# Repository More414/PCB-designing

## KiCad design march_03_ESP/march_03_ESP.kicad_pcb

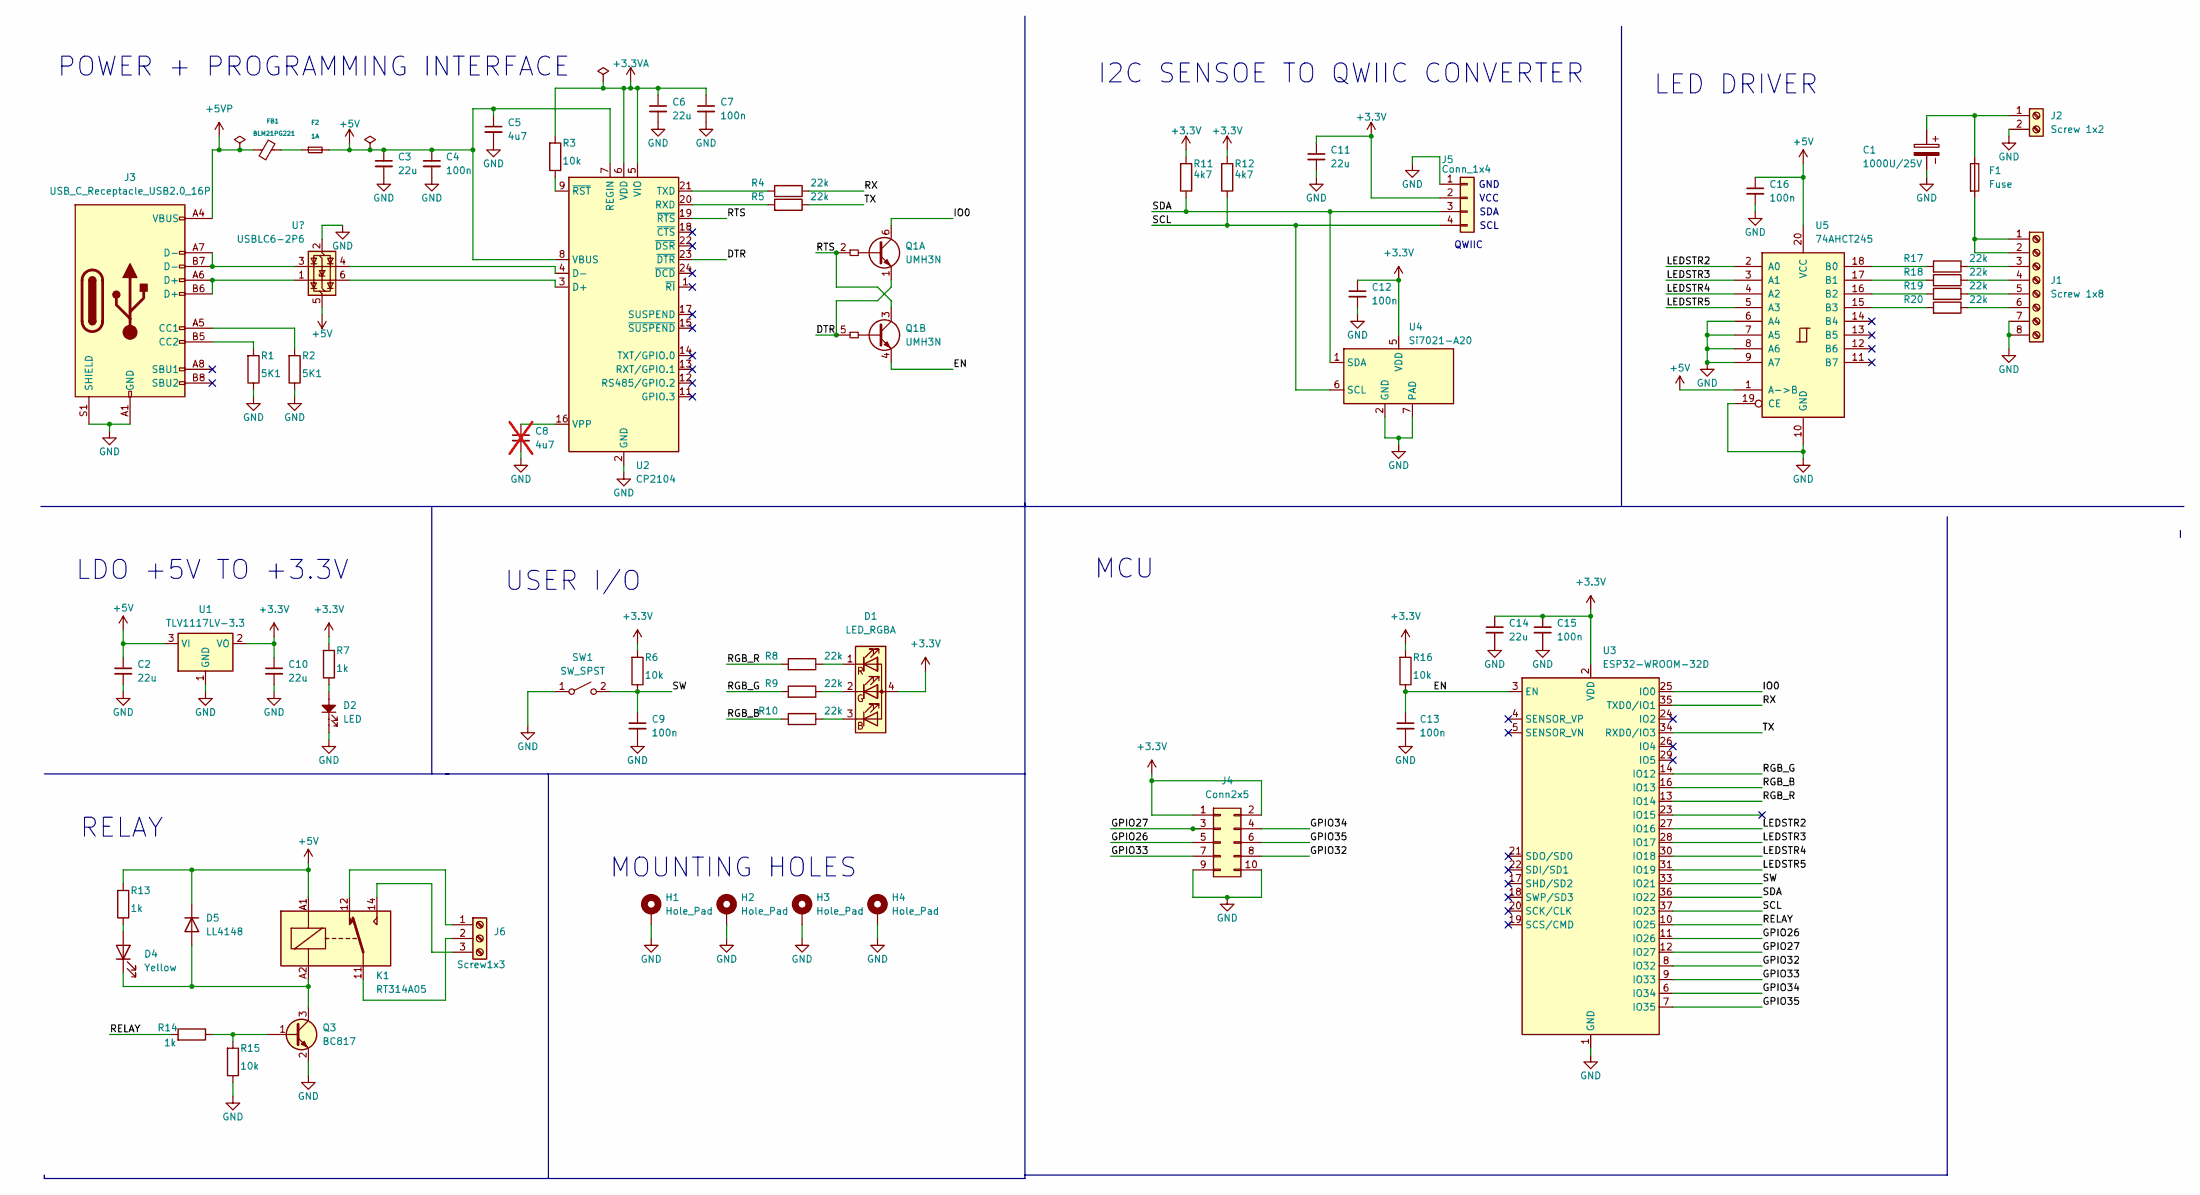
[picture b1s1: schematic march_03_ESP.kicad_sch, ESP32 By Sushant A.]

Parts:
C1: 1000U/25V; CP_Radial_D5.0mm_P2.50mm
C2, C3, C6, C10, C11, C14: 22u; C_0805_2012Metric_Pad1.18x1.45mm_HandSolder
C4, C7, C9, C12, C13, C15, C16: 100n; C_0402_1005Metric_Pad0.74x0.62mm_HandSolder
C5: 4u7; C_0805_2012Metric_Pad1.18x1.45mm_HandSolder
C8: 4u7; C_0805_2012Metric_Pad1.18x1.45mm_HandSolder; not fitted
D1: LED_RGBA; LED_RGB_Wuerth-PLCC4_3.2x2.8mm_150141M173100
D2: LED; LED_0805_2012Metric
D4: Yellow; LED_0603_1608Metric_Pad1.05x0.95mm_HandSolder
D5: LL4148; D_MiniMELF
F1: Fuse; Fuse_0805_2012Metric
F2: 1A; fuse_imp
FB1: BLM21PG221; L_0603_1608Metric_Pad1.05x0.95mm_HandSolder
H1, H2, H3, H4: Hole_Pad; MountingHole_3.2mm_M3_Pad_Via
J1: Screw 1x8; TerminalBlock_Phoenix_MKDS-1,5-8_1x08_P5.00mm_Horizontal
J2: Screw 1x2; TerminalBlock_Phoenix_MKDS-1,5-2-5.08_1x02_P5.08mm_Horizont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
J3: USB_C_Receptacle_USB2.0_16P; USB_C_Receptacle_GCT_USB4105-xx-A_16P_TopMnt_Horizontal
J4: Conn2x5; PinHeader_2x05_P2.54mm_Vertical
J5: Conn_1x4; JST_SH_SM04B-SRSS-TB_1x04-1MP_P1.00mm_Horizontal
J6: Screw1x3; TerminalBlock_Phoenix_MKDS-3-3-5.08_1x03_P5.08mm_Horizontal
K1: RT314A05; Relay_SPDT_Schrack-RT1-16A-FormC_RM5mm
Q1: UMH3N; SOT-363_SC-70-6
Q3: BC817; SOT-23
R1, R2: 5K1; R_0805_2012Metric
R3, R6, R15, R16: 10k; R_0805_2012Metric
R4, R5, R8, R9, R10, R17, R18, R19, R20: 22k; R_0805_2012Metric
R7, R13, R14: 1k; R_0805_2012Metric
R11, R12: 4k7; R_0805_2012Metric
SW1: SW_SPST; SW_Push_1P1T_NO_E-Switch_TL3301NxxxxxG
U1: TLV1117LV-3.3; SOT-223-3_TabPin2
U2: CP2104; QFN-24-1EP_4x4mm_P0.5mm_EP2.6x2.6mm
U3: ESP32-WROOM-32D
U4: Si7021-A20; DFN-6-1EP_3x3mm_P1mm_EP1.5x2.4mm
U5: 74AHCT245; DIP-20_W7.62mm

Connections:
+3.3V: C10.1, C11.1, C12.1, C14.1, C15.1, D1.4 (A), J4.1, J4.2, J5.2, R6.1, R7.1, R11.1, R12.1, R16.1, U1.2 (VO), U3.2 (VDD), U4.5 (VDD)
+3.3VA: C6.1, C7.1, R3.1, U2.5 (VIO), U2.6 (VDD)
+5V: C2.1, C3.1, C4.1, C5.1, C16.1, D5.1 (K), F2.2, K1.A1, R13.1, U1.3 (VI), U2.7 (REGIN), U2.8 (VBUS), U5.1 (A->B), U5.20 (VCC); also elsewhere on the board
+5VP: FB1.1, J3.A4 (VBUS), J3.A9 (VBUS), J3.B4 (VBUS), J3.B9 (VBUS)
/DTR: Q1.1 (E1), Q1.5 (B2), U2.23 (~DTR)
/EN: C13.1, Q1.4 (E2), R16.2, U3.3 (EN)
/GPIO26: J4.5, U3.11 (IO26)
/GPIO27: J4.3, U3.12 (IO27)
/GPIO32: J4.8, U3.8 (IO32)
/GPIO33: J4.7, U3.9 (IO33)
/GPIO34: J4.4, U3.6 (IO34)
/GPIO35: J4.6, U3.7 (IO35)
/IO0: Q1.6 (C1), U3.25 (IO0)
/LEDSTR2: U3.27 (IO16), U5.2 (A0)
/LEDSTR3: U3.28 (IO17), U5.3 (A1)
/LEDSTR4: U3.30 (IO18), U5.4 (A2)
/LEDSTR5: U3.31 (IO19), U5.5 (A3)
/RELAY: R14.1, U3.10 (IO25)
/RGB_B: R10.1, U3.16 (IO13)
/RGB_G: R9.1, U3.14 (IO12)
/RGB_R: R8.1, U3.13 (IO14)
/RTS: Q1.2 (B1), Q1.3 (C2), U2.19 (~RTS)
/RX: R4.2, U3.35 (TXD0/IO1)
/SCL: J5.4, R12.2, U3.37 (IO23), U4.6 (SCL)
/SDA: J5.3, R11.2, U3.36 (IO22), U4.1 (SDA)
/SW: C9.1, R6.2, SW1.2 (B), U3.33 (IO21)
/TX: R5.2, U3.34 (RXD0/IO3)
GND: C1.2, C2.2, C3.2, C4.2, C5.2, C6.2, C7.2, C8.2, C9.2, C10.2, C11.2, C12.2, C13.2, C14.2, C15.2, C16.2, D2.1, H1.1, H2.1, H3.1, H4.1, J1.7, J1.8, J2.2, J3.A1 (GND), J3.A12 (GND), J3.B1 (GND), J3.B12 (GND), J3.S1 (SHIELD), J4.9, J4.10, J5.1, Q3.2 (E), R1.2, R2.2, R15.2, SW1.1 (A), U1.1 (GND), U2.2 (GND), U2.25 (GND), U3.1 (GND), U3.15 (GND), U3.38 (GND), U3.39 (GND), U4.2 (GND), U4.7 (PAD), U5.6 (A4), U5.7 (A5), U5.8 (A6), U5.9 (A7), U5.10 (GND), U5.19 (CE); also elsewhere on the board
unnamed: D1.3 (BK), R10.2
unnamed: D1.2 (GK), R9.2
unnamed: D1.1 (RK), R8.2
unnamed: D2.2, R7.2
unnamed: D4.2 (A), R13.2
unnamed: D4.1 (K), D5.2 (A), K1.A2, Q3.3 (C)
unnamed: F2.1, FB1.2
unnamed: F1.2, J1.1, J1.2
unnamed: J1.3, R17.2
unnamed: J1.4, R18.2
unnamed: J1.5, R19.2
unnamed: J1.6, R20.2
unnamed: C1.1, F1.1, J2.1
unnamed: J3.A5 (CC1), R2.1
unnamed: J3.B5 (CC2), R1.1
unnamed 43: J3.A6 (D+), J3.B6 (D+); also elsewhere on the board
unnamed 44: J3.A7 (D-), J3.B7 (D-); also elsewhere on the board
unnamed: J6.1, K1.12
unnamed: J6.2, K1.11
unnamed: J6.3, K1.14
unnamed: Q3.1 (B), R14.2, R15.1
unnamed 49: U2.3 (D+); also elsewhere on the board
unnamed 50: U2.4 (D-); also elsewhere on the board
unnamed: R5.1, U2.20 (RXD)
unnamed: R4.1, U2.21 (TXD)
unnamed: C8.1, U2.16 (VPP)
unnamed: R3.2, U2.9 (~RST)
unnamed: R17.1, U5.18 (B0)
unnamed: R18.1, U5.17 (B1)
unnamed: R19.1, U5.16 (B2)
unnamed: R20.1, U5.15 (B3)

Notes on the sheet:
LED DRIVER
I2C SENSOE TO QWIIC CONVERTER
VCC
MOUNTING HOLES
SDA
LDO +5V TO +3.3V
POWER + PROGRAMMING INTERFACE
MCU
USER I/O
GND
RELAY
SCL
QWIIC

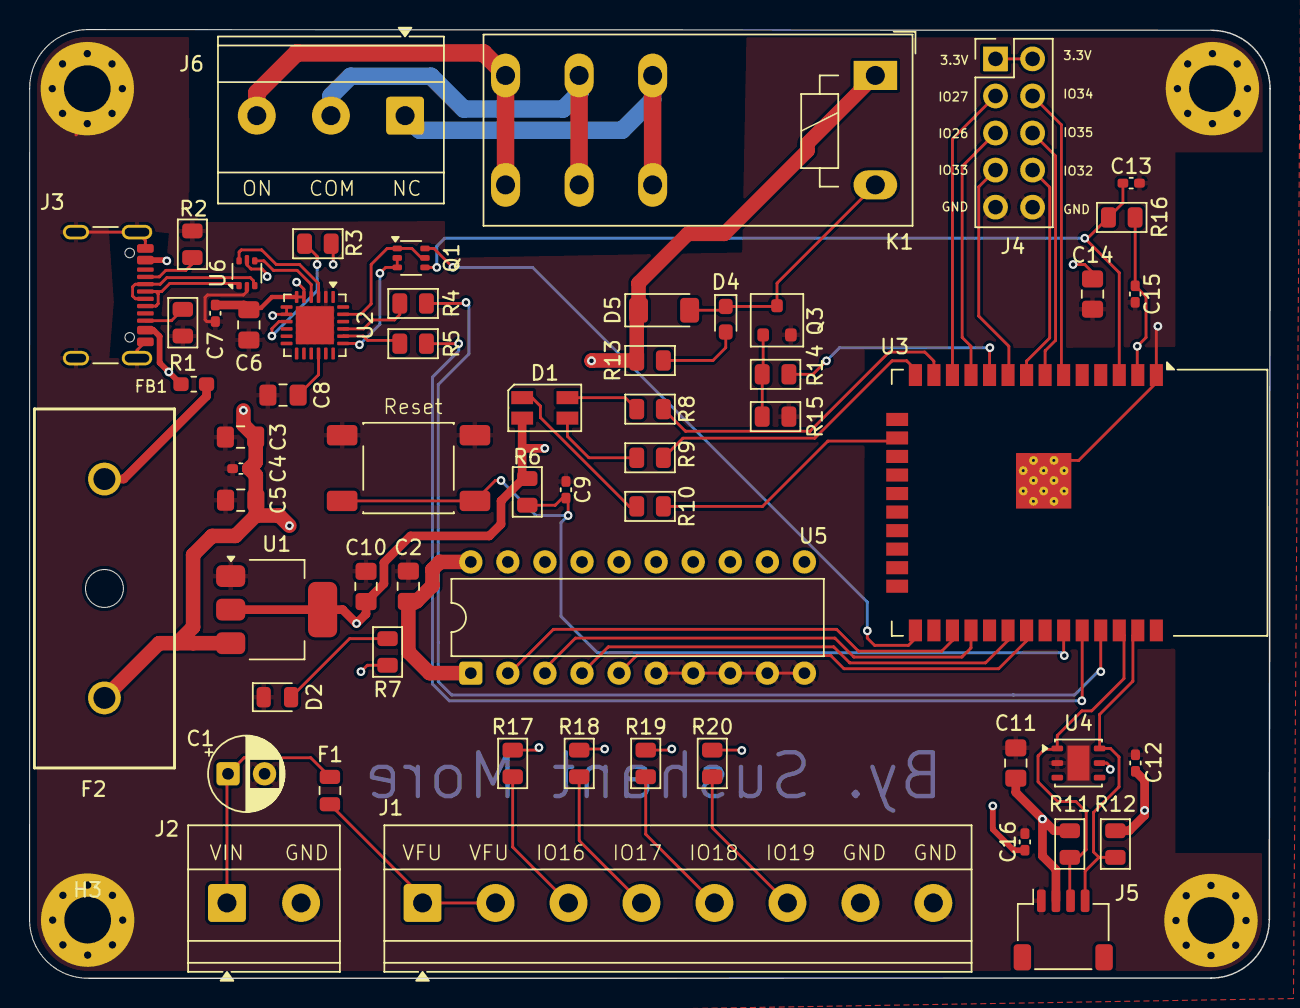
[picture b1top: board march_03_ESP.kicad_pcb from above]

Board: 4 copper layers, 85.0 x 65.0 mm, 63 parts (0 on the bottom side), 59 nets.

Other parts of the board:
U6: USBLC6-2P6; SOT-666

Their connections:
+5V: U6.5 (VBUS); also elsewhere on the board
GND: U6.2 (GND); also elsewhere on the board
unnamed 43: U6.1 (I/O1); also elsewhere on the board
unnamed 44: U6.3 (I/O2); also elsewhere on the board
unnamed 49: U6.6 (I/O1); also elsewhere on the board
unnamed 50: U6.4 (I/O2); also elsewhere on the board

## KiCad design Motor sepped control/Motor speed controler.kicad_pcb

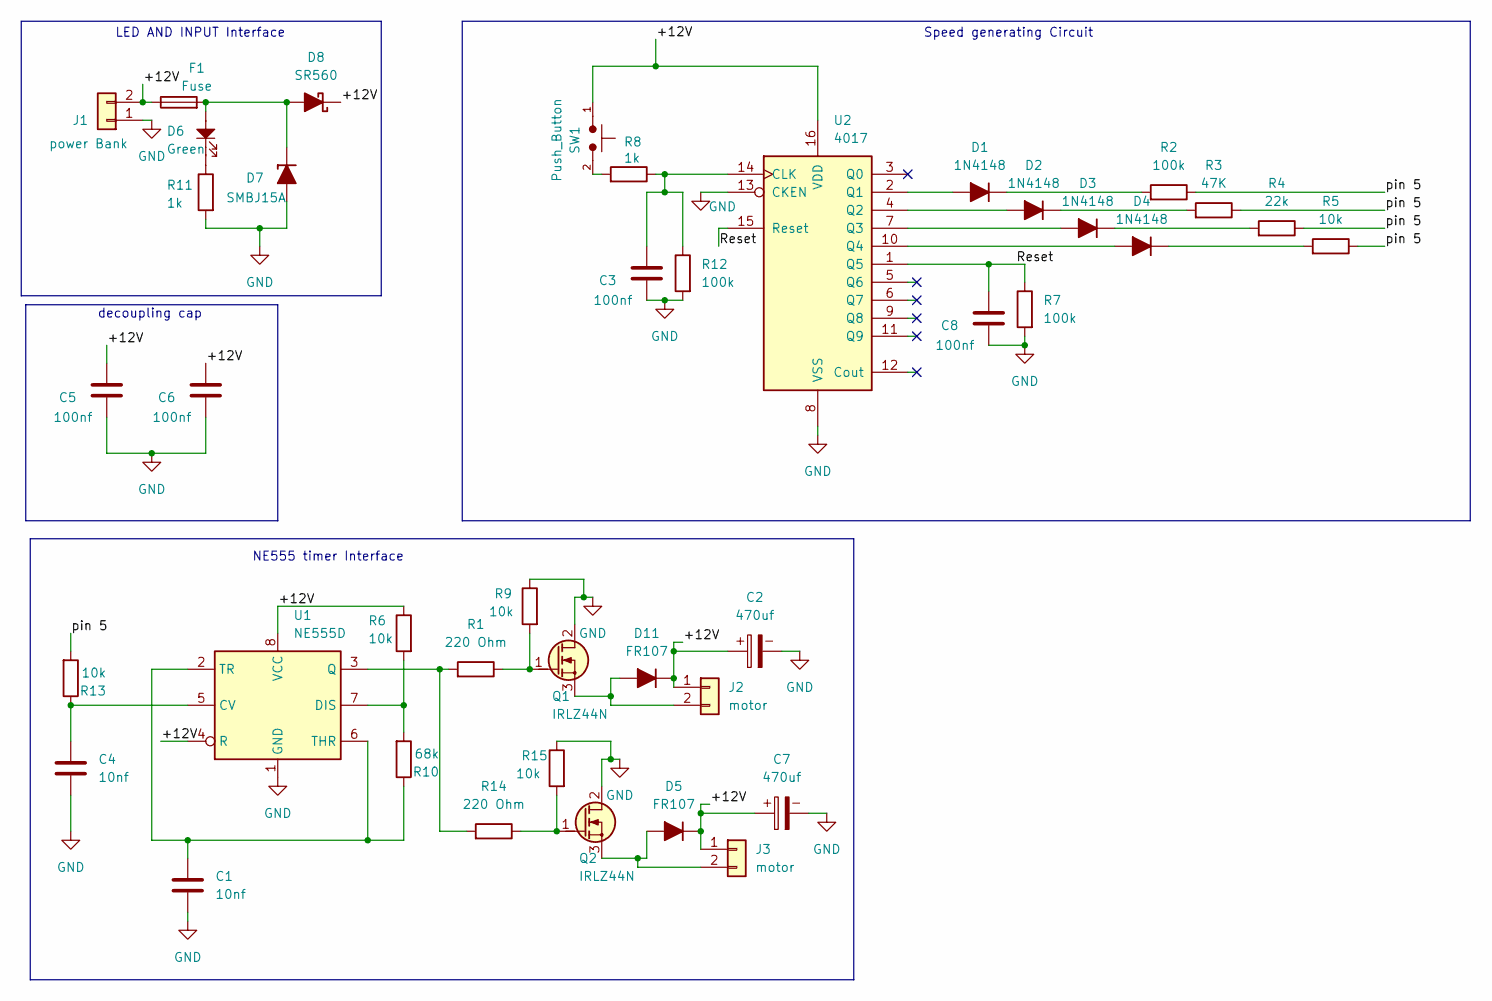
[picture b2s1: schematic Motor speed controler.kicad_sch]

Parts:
C1, C4: 10nf; C_0603_1608Metric
C2, C7: 470uf; CP_Radial_D6.3mm_P2.50mm
C3, C5, C6, C8: 100nf; C_0603_1608Metric
D1, D2, D3, D4: 1N4148; D_SOD-123
D5, D11: FR107; D_0603_1608Metric
D6: Green; LED_1206_3216Metric
D7: SMBJ15A; D_0603_1608Metric
D8: SR560; D_2114_3652Metric
F1: Fuse; Fuse_1206_3216Metric
J1: power Bank; PhoenixContact_MC_1,5_2-G-3.81_1x02_P3.81mm_Horizontal
J2, J3: motor; PhoenixContact_MC_1,5_2-G-3.81_1x02_P3.81mm_Horizontal
Q1, Q2: IRLZ44N; TO-220-3_Horizontal_TabDown
R1, R14: 220 Ohm; R_0603_1608Metric
R2, R7, R12: 100k; R_0603_1608Metric
R3: 47K; R_0603_1608Metric
R4: 22k; R_0603_1608Metric
R5, R6, R9, R13, R15: 10k; R_0603_1608Metric
R8, R11: 1k; R_0603_1608Metric
R10: 68k; R_0603_1608Metric
SW1: Push_Button; SW_PUSH_6mm
U1: NE555D; SOIC-8_3.9x4.9mm_P1.27mm
U2: 4017; JEITA_SOIC-16_3.9x9.9mm_P1.27mm

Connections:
/+12V: C2.1, C5.1, C6.1, C7.1, D5.1 (K), D8.1 (K), D11.1 (K), F1.1, J1.2, J2.1, J3.1, R6.2, SW1.1, U1.4 (R), U1.8 (VCC), U2.16 (VDD)
/Reset: C8.1, R7.2, U2.1 (Q5), U2.15 (Reset)
/pin 5: R2.2, R3.2, R4.2, R5.2, R13.1
GND: C1.2, C2.2, C3.2, C4.2, C5.2, C6.2, C7.2, C8.2, D7.2 (A), J1.1, Q1.2 (D), Q2.2 (D), R7.1, R9.2, R11.1, R12.1, R15.2, U1.1 (GND), U2.8 (VSS), U2.13 (CKEN)
unnamed: D1.2 (A), U2.2 (Q1)
unnamed: D1.1 (K), R2.1
unnamed: D2.2 (A), U2.4 (Q2)
unnamed: D2.1 (K), R3.1
unnamed: D3.2 (A), U2.7 (Q3)
unnamed: D3.1 (K), R4.1
unnamed: D4.2 (A), U2.10 (Q4)
unnamed: D4.1 (K), R5.1
unnamed: D5.2 (A), J3.2, Q2.3 (S)
unnamed: D6.1, R11.2
unnamed: D6.2, D7.1 (K), D8.2 (A), F1.2
unnamed: D11.2 (A), J2.2, Q1.3 (S)
unnamed: Q1.1 (G), R1.2, R9.1
unnamed: Q2.1 (G), R14.2, R15.1
unnamed: R8.1, SW1.2
unnamed: C4.1, R13.2, U1.5 (CV)
unnamed: R6.1, R10.1, U1.7 (DIS)
unnamed: R1.1, R14.1, U1.3 (Q)
unnamed: C1.1, R10.2, U1.2 (TR), U1.6 (THR)
unnamed: C3.1, R8.2, R12.2, U2.14 (CLK)

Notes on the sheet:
NE555 timer Interface
Speed generating Circuit
decoupling cap
LED AND INPUT Interface

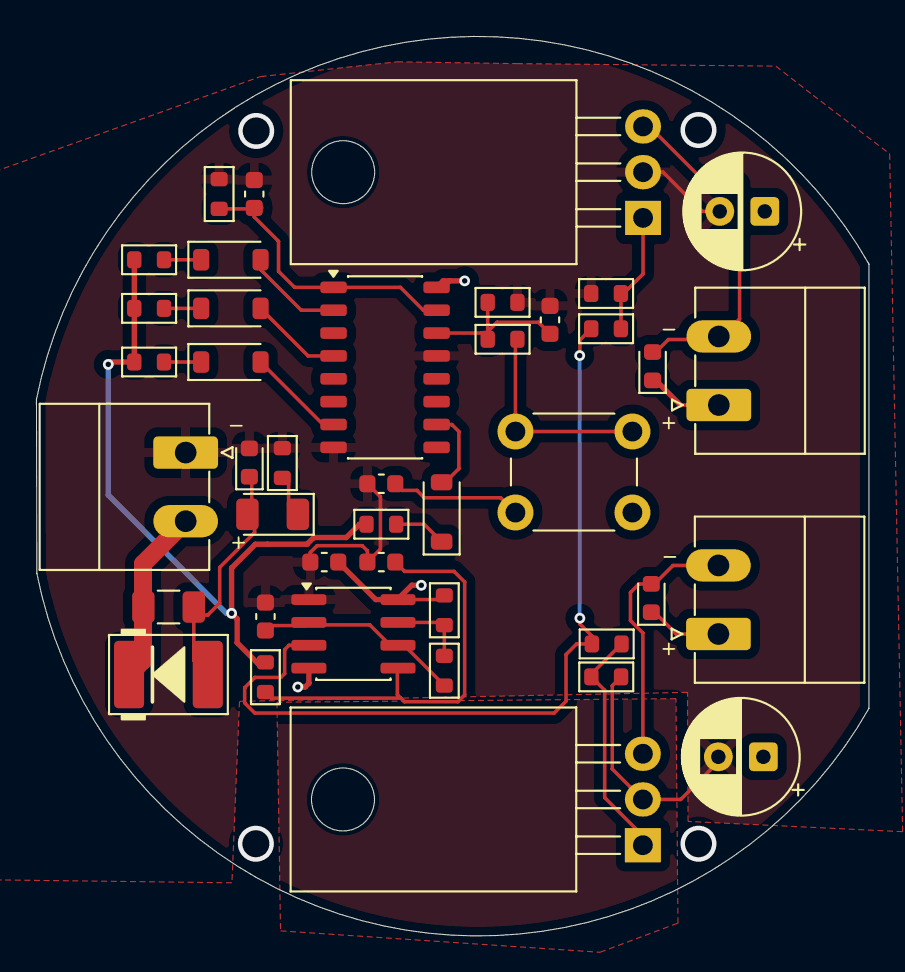
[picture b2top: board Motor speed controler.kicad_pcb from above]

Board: 2 copper layers, 46.2 x 50.0 mm, 41 parts (0 on the bottom side), 24 nets.

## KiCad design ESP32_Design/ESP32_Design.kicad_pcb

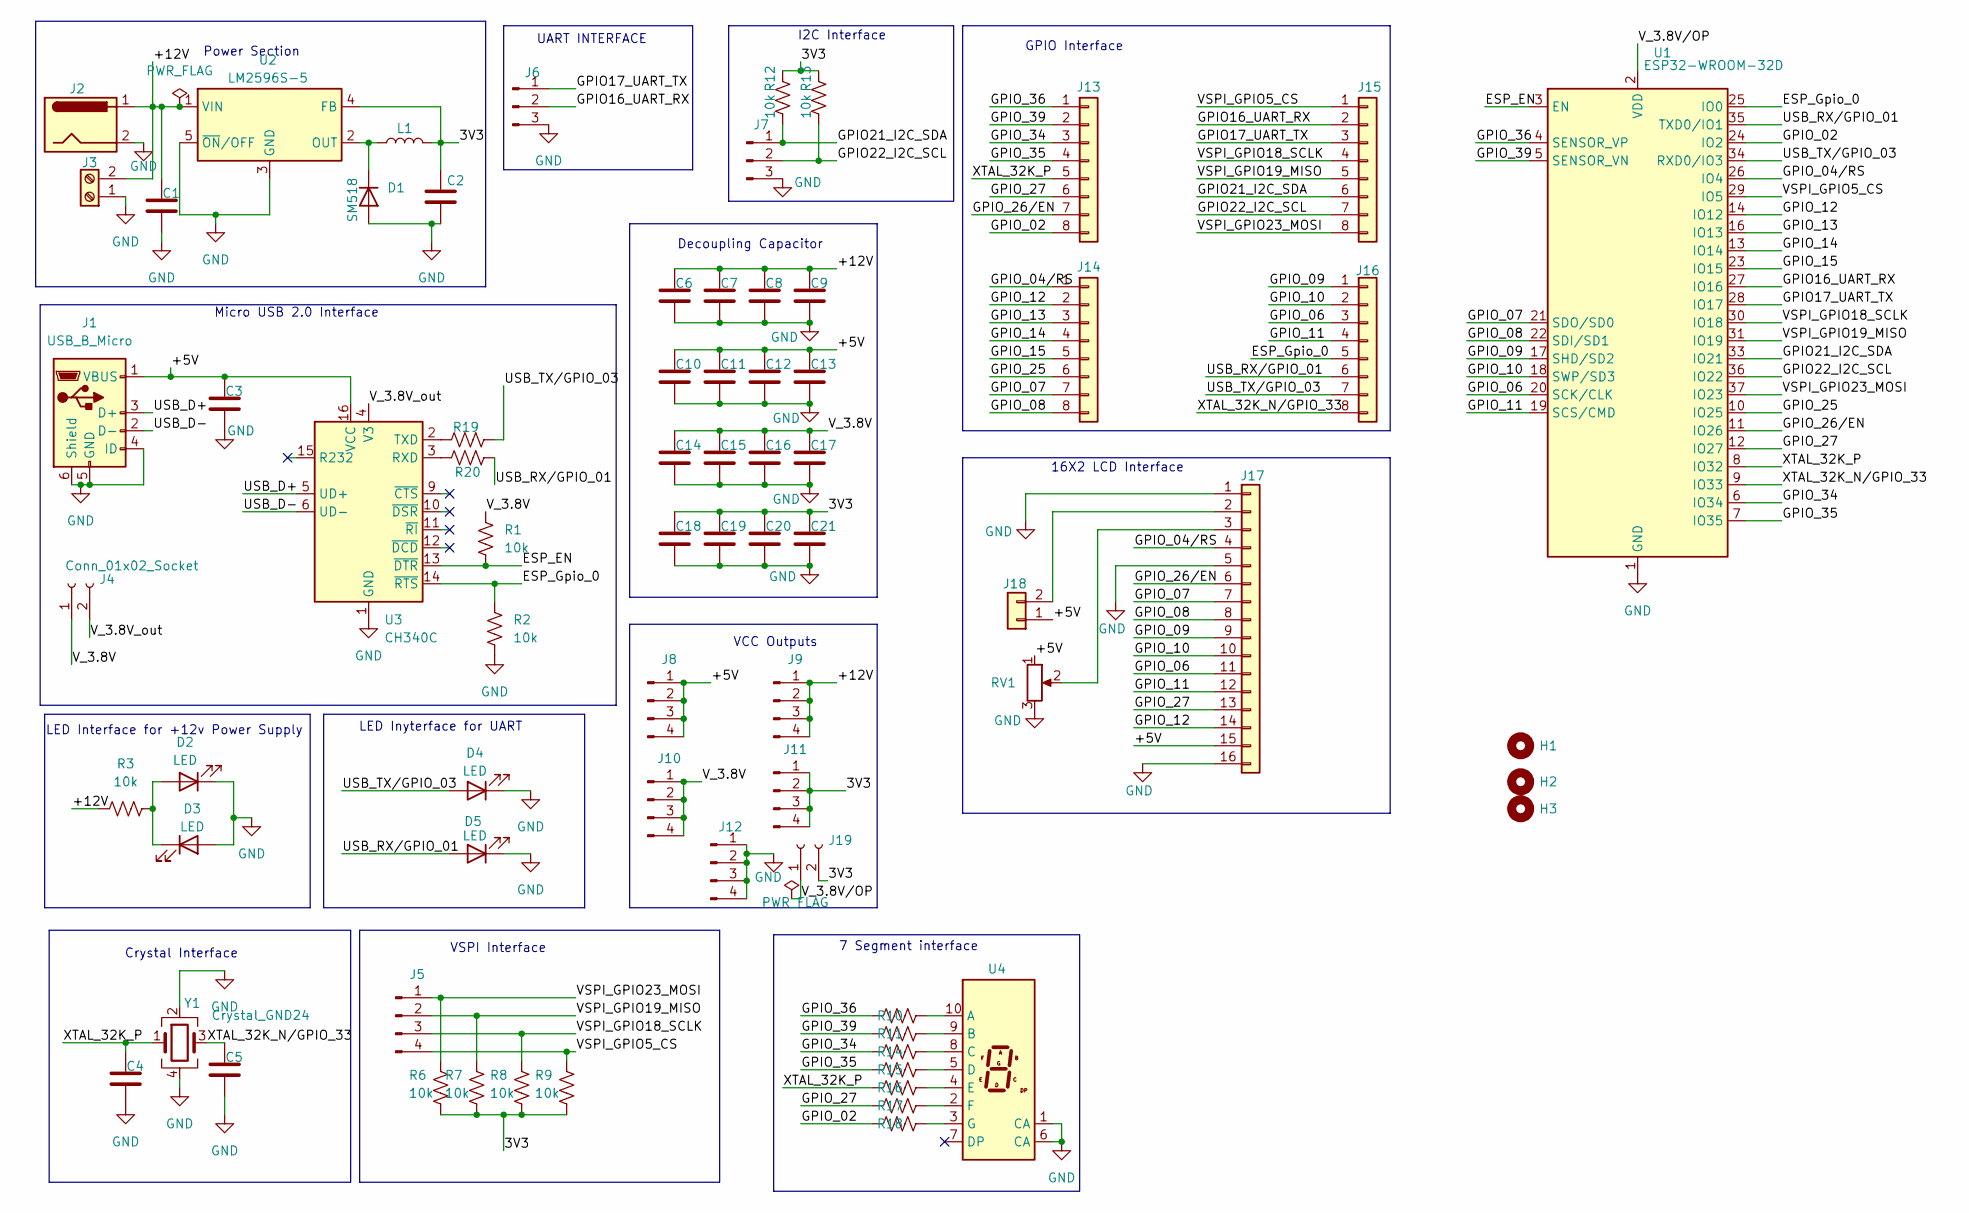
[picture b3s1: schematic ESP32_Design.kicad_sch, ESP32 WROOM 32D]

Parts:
C1, C2, C3, C4, C5, C6, C7, C8, C9, C10, C11, C12, C13, C14, C15, C16, C17, C18, C19, C20, C21: C; C_0805_2012Metric_Pad1.18x1.45mm_HandSolder
D1: SM518; D_DO-41_SOD81_P2.54mm_Vertical_AnodeUp
D2, D3, D4, D5: LED; LED_0805_2012Metric
H1, H2, H3: MountingHole; MountingHole_2.2mm_M2_DIN965_Pad
J1: USB_B_Micro; USB_Micro-B_Molex_47346-0001
J2: Jack-DC; BarrelJack_SwitchcraftConxall_RAPC10U_Horizontal
J3: Screw_Terminal_01x02; TerminalBlock_Philmore_TB132_1x02_P5.00mm_Horizontal
J4: Conn_01x02_Socket; Molex_SL_171971-0002_1x02_P2.54mm_Vertical
J5, J8, J9, J10, J11, J12: Conn_01x04_Pin; FanPinHeader_1x04_P2.54mm_Vertical
J6, J7: Conn_01x03_Pin; FanPinHeader_1x03_P2.54mm_Vertical
J13, J14, J15, J16: Conn_01x08; Molex_KK-254_AE-6410-08A_1x08_P2.54mm_Vertical
J17: Conn_01x16; PinHeader_1x16_P2.54mm_Vertical
J18: Conn_01x02; PinHeader_1x02_P2.54mm_Vertical
J19: Conn_01x02_Socket; Molex_KK-254_AE-6410-02A_1x02_P2.54mm_Vertical
L1: L; L_0805_2012Metric_Pad1.05x1.20mm_HandSolder
R1, R2, R3, R6, R7, R8, R9, R10, R11, R12, R13, R14, R15, R16, R17, R18, R19, R20: 10k; R_0805_2012Metric_Pad1.20x1.40mm_HandSolder
RV1: R_Potentiometer; Potentiometer_Vishay_148-149_Single_Horizontal
U1: ESP32-WROOM-32D
U2: LM2596S-5; TO-263-5_TabPin3
U3: CH340C; SOIC-16_3.9x9.9mm_P1.27mm
U4: HDSP-7401
Y1: Crystal_GND24; Crystal_SMD_0603-4Pin_6.0x3.5mm

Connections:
/3V3: C2.1, C18.1, C19.1, C20.1, C21.1, J11.1, J11.2, J11.3, J11.4, J19.2, L1.2, R6.2, R7.2, R8.2, R9.2, R12.1, R13.1, U2.4 (FB)
/+5V: C3.1, C10.1, C11.1, C12.1, C13.1, J1.1 (VBUS), J8.1, J8.2, J8.3, J8.4, J17.15, J18.1, RV1.1, U3.16 (VCC)
/+12V: C1.1, C6.1, C7.1, C8.1, C9.1, J2.1, J3.2, J9.1, J9.2, J9.3, J9.4, R3.1, U2.1 (VIN)
/ESP_EN: R1.2, U1.3 (EN), U3.13 (~DTR)
/ESP_Gpio_0: J16.5, R2.1, U1.25 (IO0), U3.14 (~RTS)
/GPIO16_UART_RX: J6.2, J15.2, U1.27 (IO16)
/GPIO17_UART_TX: J6.1, J15.3, U1.28 (IO17)
/GPIO21_I2C_SDA: J7.1, J15.6, R12.2, U1.33 (IO21)
/GPIO22_I2C_SCL: J7.2, J15.7, R13.2, U1.36 (IO22)
/GPIO_02: J13.8, R18.2, U1.24 (IO2)
/GPIO_04/RS: J14.1, J17.4, U1.26 (IO4)
/GPIO_06: J16.3, J17.11, U1.20 (SCK/CLK)
/GPIO_07: J14.7, J17.7, U1.21 (SDO/SD0)
/GPIO_08: J14.8, J17.8, U1.22 (SDI/SD1)
/GPIO_09: J16.1, J17.9, U1.17 (SHD/SD2)
/GPIO_10: J16.2, J17.10, U1.18 (SWP/SD3)
/GPIO_11: J16.4, J17.12, U1.19 (SCS/CMD)
/GPIO_12: J14.2, J17.14, U1.14 (IO12)
/GPIO_13: J14.3, U1.16 (IO13)
/GPIO_14: J14.4, U1.13 (IO14)
/GPIO_15: J14.5, U1.23 (IO15)
/GPIO_25: J14.6, U1.10 (IO25)
/GPIO_26/EN: J13.7, J17.6, U1.11 (IO26)
/GPIO_27: J13.6, J17.13, R17.2, U1.12 (IO27)
/GPIO_34: J13.3, R14.2, U1.6 (IO34)
/GPIO_35: J13.4, R15.2, U1.7 (IO35)
/GPIO_36: J13.1, R10.2, U1.4 (SENSOR_VP)
/GPIO_39: J13.2, R11.2, U1.5 (SENSOR_VN)
/USB_D+: J1.3 (D+), U3.5 (UD+)
/USB_D-: J1.2 (D-), U3.6 (UD-)
/USB_RX/GPIO_01: D5.2 (A), J16.6, R20.2, U1.35 (TXD0/IO1)
/USB_TX/GPIO_03: D4.2 (A), J16.7, R19.2, U1.34 (RXD0/IO3)
/VSPI_GPIO5_CS: J5.4, J15.1, R9.1, U1.29 (IO5)
/VSPI_GPIO18_SCLK: J5.3, J15.4, R8.1, U1.30 (IO18)
/VSPI_GPIO19_MISO: J5.2, J15.5, R7.1, U1.31 (IO19)
/VSPI_GPIO23_MOSI: J5.1, J15.8, R6.1, U1.37 (IO23)
/V_3.8V: C14.1, C15.1, C16.1, C17.1, J4.1, J10.1, J10.2, J10.3, J10.4, R1.1
/V_3.8V_out: J4.2, U3.4 (V3)
/V_3.8V/OP: J19.1, U1.2 (VDD)
/XTAL_32K_N/GPIO_33: C5.1, J16.8, U1.9 (IO33), Y1.3
/XTAL_32K_P: C4.1, J13.5, R16.2, U1.8 (IO32), Y1.1
GND: C1.2, C2.2, C3.2, C4.2, C5.2, C6.2, C7.2, C8.2, C9.2, C10.2, C11.2, C12.2, C13.2, C14.2, C15.2, C16.2, C17.2, C18.2, C19.2, C20.2, C21.2, D1.2 (A), D2.1 (K), D3.2 (A), D4.1 (K), D5.1 (K), J1.4 (ID), J1.5 (GND), J1.6 (Shield), J2.2, J3.1, J6.3, J7.3, J12.1, J12.2, J12.3, J12.4, J17.1, J17.5, J17.16, R2.2, RV1.3, U1.1 (GND), U1.15 (GND), U1.38 (GND), U1.39 (GND), U2.3 (GND), U2.5 (~ON/OFF), U3.1 (GND), U4.1 (CA), U4.6 (CA), Y1.2, Y1.4
unnamed: D1.1 (K), L1.1, U2.2 (OUT)
unnamed: D2.2 (A), D3.1 (K), R3.2
unnamed: J17.2, J18.2
unnamed: J17.3, RV1.2
unnamed: R20.1, U3.3 (RXD)
unnamed: R19.1, U3.2 (TXD)
unnamed: R10.1, U4.10 (A)
unnamed: R11.1, U4.9 (B)
unnamed: R14.1, U4.8 (C)
unnamed: R15.1, U4.5 (D)
unnamed: R16.1, U4.4 (E)
unnamed: R17.1, U4.2 (F)
unnamed: R18.1, U4.3 (G)

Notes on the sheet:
16X2 LCD Interface
LED Inyterface for UART
7 Segment interface
Decoupling Capacitor
LED Interface for +12v Power Supply
GPIO Interface
Micro USB 2.0 Interface
VSPI Interface
UART INTERFACE
VCC Outputs
I2C Interface
Power Section
Crystal Interface

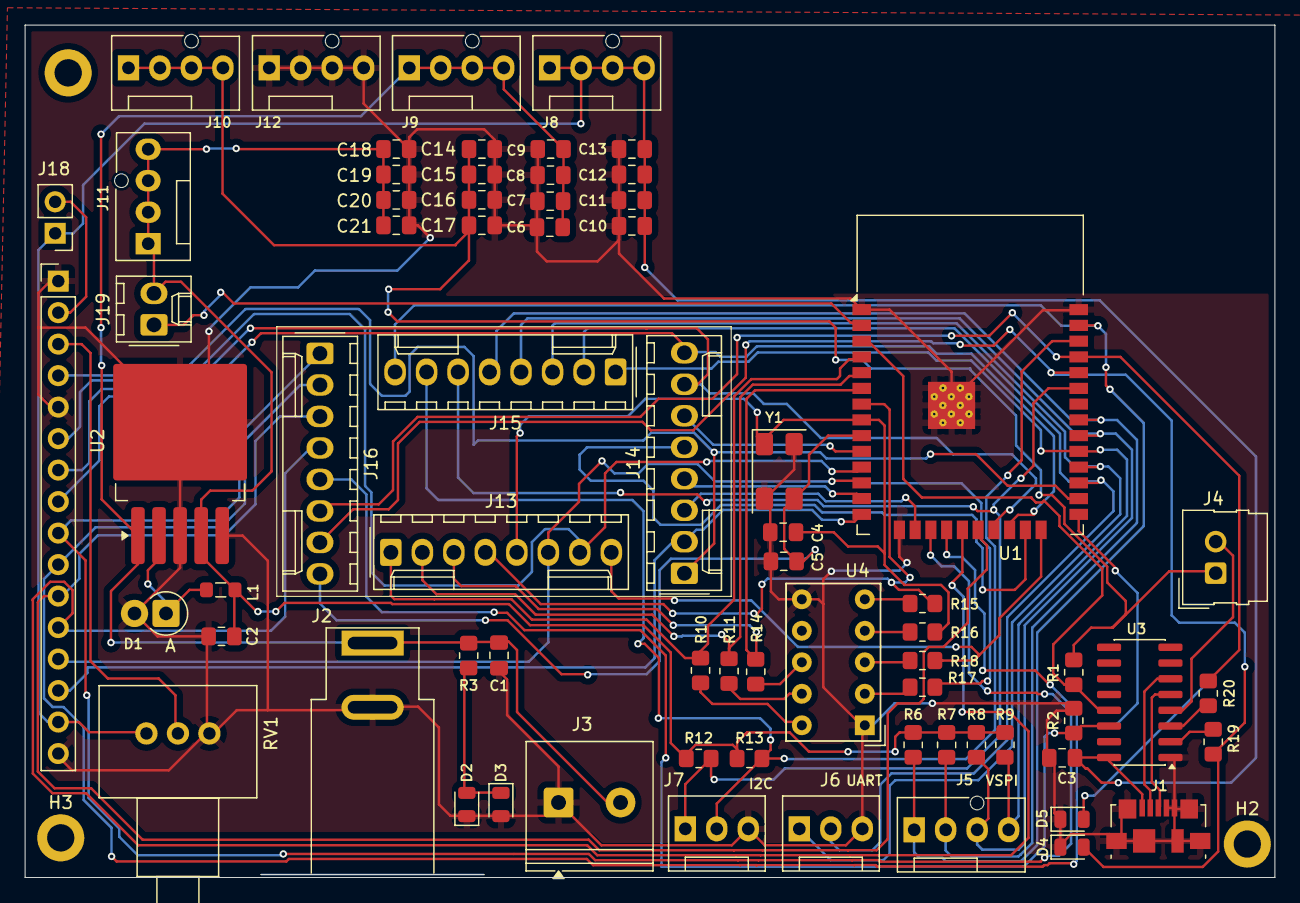
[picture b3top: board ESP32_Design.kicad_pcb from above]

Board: 2 copper layers, 100.7 x 68.7 mm, 73 parts (0 on the bottom side), 55 nets.

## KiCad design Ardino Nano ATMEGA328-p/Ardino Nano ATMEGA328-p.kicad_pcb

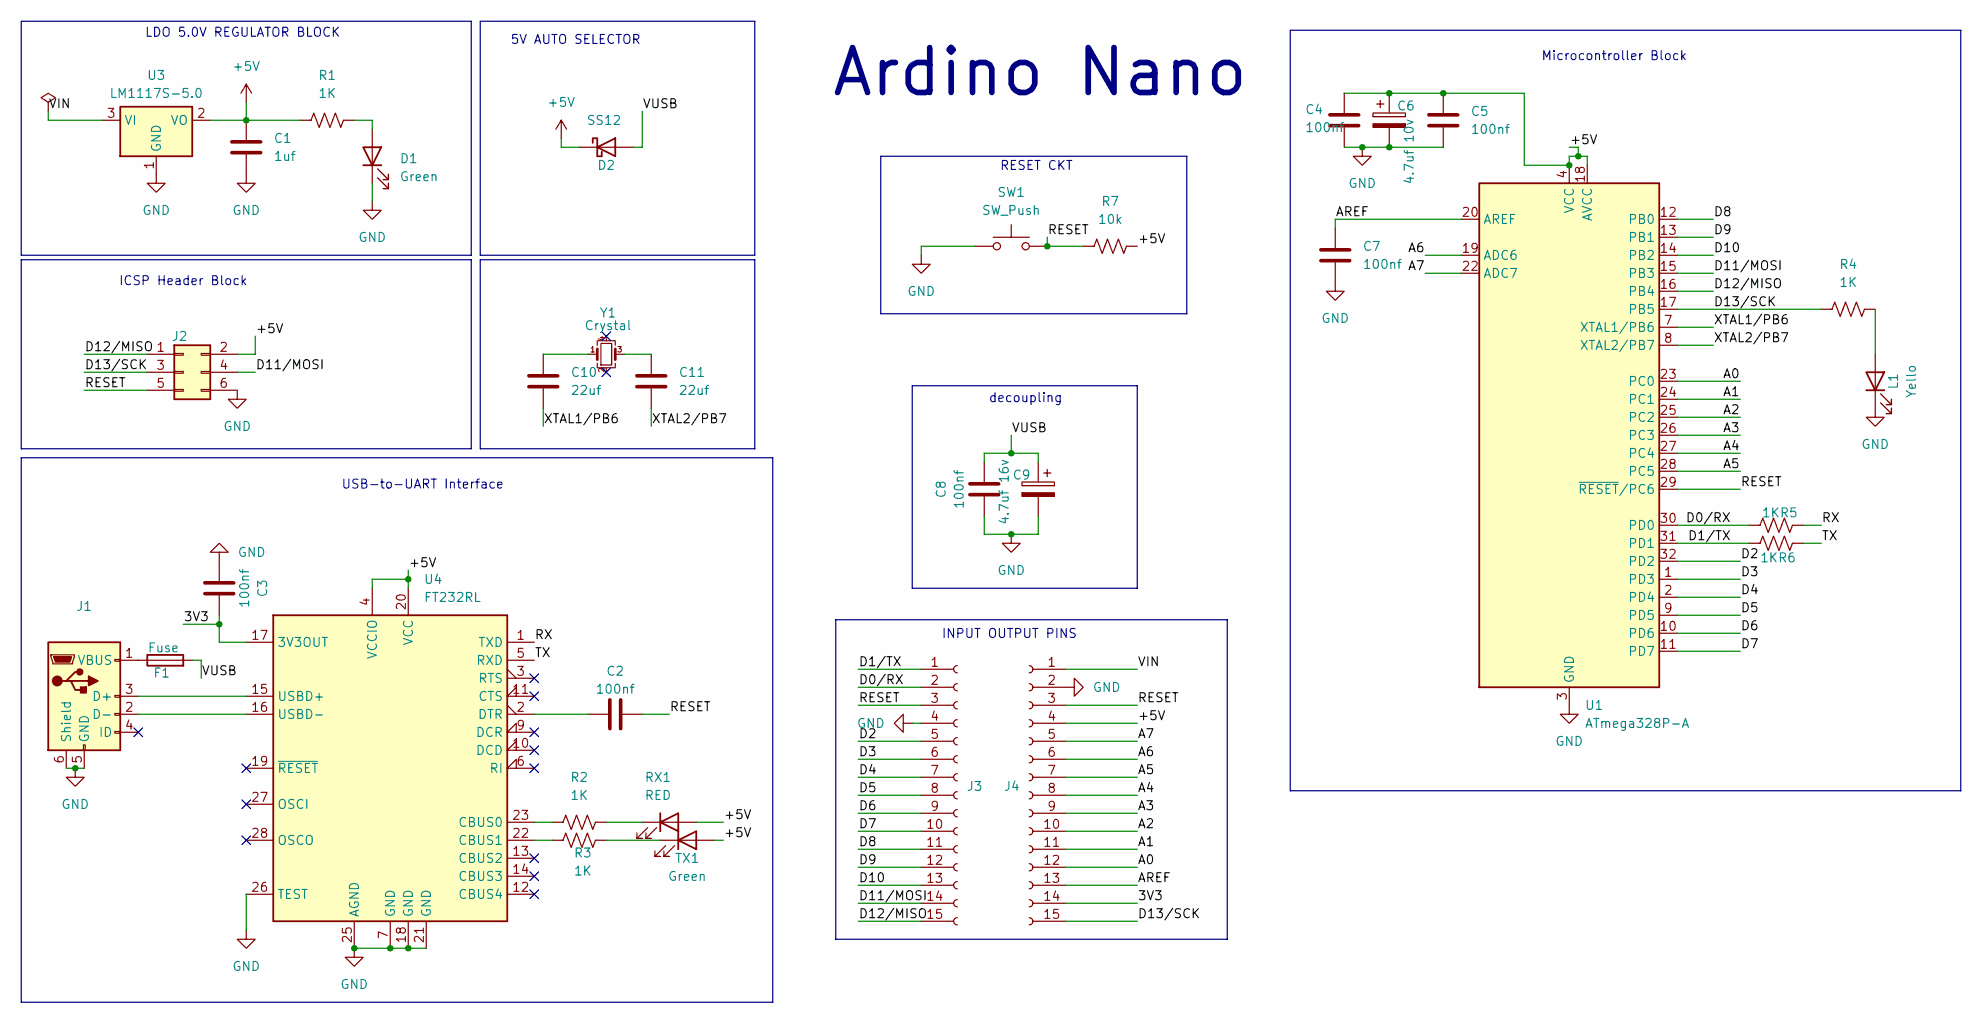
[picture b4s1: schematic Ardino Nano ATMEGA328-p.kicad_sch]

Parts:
C1: 1uf; C_0805_2012Metric_Pad1.18x1.45mm_HandSolder
C2, C3, C4, C5, C7, C8: 100nf; C_0805_2012Metric_Pad1.18x1.45mm_HandSolder
C6: 4.7uf 10v; C_0805_2012Metric
C9: 4.7uf 16v; C_0805_2012Metric
C10, C11: 22uf; C_0805_2012Metric_Pad1.18x1.45mm_HandSolder
D1: Green; LED_0603_1608Metric
D2: SS12; D_SOD-123F
F1: Fuse; Fuse_1206_3216Metric_Pad1.42x1.75mm_HandSolder
J1: USB_B_Micro; USB_Micro-B_Molex_47346-0001
J2: Conn_02x03_Odd_Even; PinHeader_2x03_P2.54mm_Vertical
J3, J4: Conn_01x15_Socket; PinHeader_1x15_P2.54mm_Vertical
L1: Yello; LED_0603_1608Metric
R1, R2, R3, R4, R5, R6: 1K; R_0805_2012Metric
R7: 10k; R_0805_2012Metric
RX1: RED; LED_0603_1608Metric
SW1: SW_Push; SW_PUSH_1P1T_6x3.5mm_H5.0_APEM_MJTP1250
TX1: Green; LED_0603_1608Metric
U1: ATmega328P-A; TQFP-32_7x7mm_P0.8mm
U3: LM1117S-5.0; SOT-223-3_TabPin2
U4: FT232RL; SSOP-28_5.3x10.2mm_P0.65mm
Y1: Crystal; Crystal_SMD_3225-4Pin_3.2x2.5mm

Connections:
+5V: C1.1, C4.1, C5.1, C6.1, D2.1 (K), J2.2, J4.4, R1.1, R7.2, RX1.2 (A), TX1.2 (A), U1.4 (VCC), U1.6 (VCC), U1.18 (AVCC), U3.2 (VO), U4.4 (VCCIO), U4.20 (VCC)
/3V3: C3.2, J4.14, U4.17 (3V3OUT)
/A0: J4.12, U1.23 (PC0)
/A1: J4.11, U1.24 (PC1)
/A2: J4.10, U1.25 (PC2)
/A3: J4.9, U1.26 (PC3)
/A4: J4.8, U1.27 (PC4)
/A5: J4.7, U1.28 (PC5)
/A6: J4.6, U1.19 (ADC6)
/A7: J4.5, U1.22 (ADC7)
/AREF: C7.1, J4.13, U1.20 (AREF)
/D0/RX: J3.2, R5.1, U1.30 (PD0)
/D1/TX: J3.1, R6.1, U1.31 (PD1)
/D2: J3.5, U1.32 (PD2)
/D3: J3.6, U1.1 (PD3)
/D4: J3.7, U1.2 (PD4)
/D5: J3.8, U1.9 (PD5)
/D6: J3.9, U1.10 (PD6)
/D7: J3.10, U1.11 (PD7)
/D8: J3.11, U1.12 (PB0)
/D9: J3.12, U1.13 (PB1)
/D10: J3.13, U1.14 (PB2)
/D11/MOSI: J2.4, J3.14, U1.15 (PB3)
/D12/MISO: J2.1, J3.15, U1.16 (PB4)
/D13/SCK: J2.3, J4.15, R4.1, U1.17 (PB5)
/RESET: C2.2, J2.5, J3.3, J4.3, R7.1, SW1.2, U1.29 (~RESET/PC6); also elsewhere on the board
/RX: R5.2, U4.1 (TXD)
/TX: R6.2, U4.5 (RXD)
/VIN: J4.1, U3.3 (VI)
/VUSB: C8.2, C9.1, D2.2 (A), F1.2
/XTAL1/PB6: C10.2, U1.7 (XTAL1/PB6)
/XTAL2/PB7: C11.2, U1.8 (XTAL2/PB7)
GND: C1.2, C3.1, C4.2, C5.2, C6.2, C7.2, C8.1, C9.2, D1.1 (K), J1.5 (GND), J1.6 (Shield), J2.6, J3.4, J4.2, L1.1 (K), SW1.1, U1.3 (GND), U1.5 (GND), U1.21 (GND), U3.1 (GND), U4.7 (GND), U4.18 (GND), U4.21 (GND), U4.25 (AGND), U4.26 (TEST); also elsewhere on the board
unnamed: C10.1, Y1.1
unnamed: C11.1, Y1.3
unnamed 35: D1.2 (A), R1.2; also elsewhere on the board
unnamed: J1.3 (D+), U4.15 (USBD+)
unnamed: J1.2 (D-), U4.16 (USBD-)
unnamed: F1.1, J1.1 (VBUS)
unnamed: L1.2 (A), R4.2
unnamed: R2.2, RX1.1 (K)
unnamed: R3.2, TX1.1 (K)
unnamed: R2.1, U4.23 (CBUS0)
unnamed: R3.1, U4.22 (CBUS1)
unnamed: C2.1, U4.2 (DTR)

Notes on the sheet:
ICSP Header Block
INPUT OUTPUT PINS
LDO 5.0V REGULATOR BLOCK
Ardino Nano
5V AUTO SELECTOR
decoupling
RESET CKT
USB-to-UART Interface
Microcontroller Block

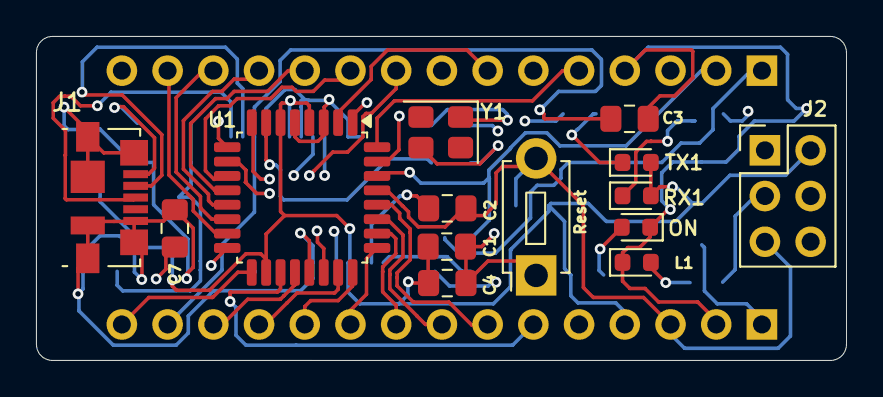
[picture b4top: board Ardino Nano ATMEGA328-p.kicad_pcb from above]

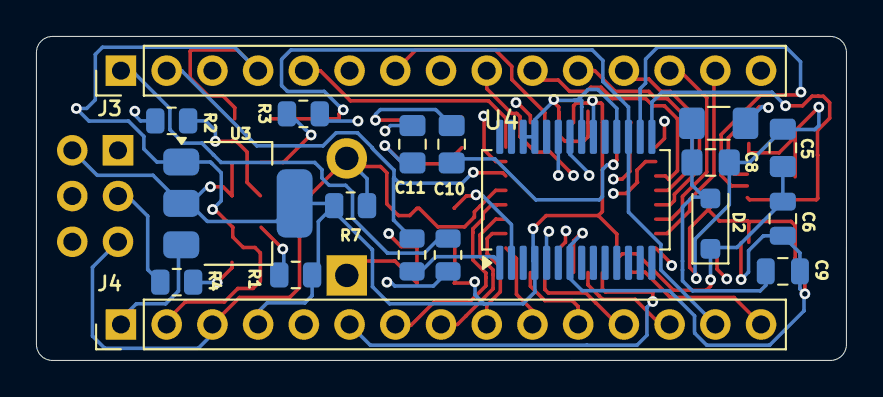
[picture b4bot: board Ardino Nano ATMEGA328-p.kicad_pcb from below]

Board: 4 copper layers, 45.0 x 18.0 mm, 33 parts (19 on the bottom side), 45 nets.

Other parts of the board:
ON: Green; LED_0603_1608Metric
Reset: SW_Push; SW_PUSH_1P1T_6x3.5mm_H5.0_APEM_MJTP1250

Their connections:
/RESET: Reset.2; also elsewhere on the board
GND: ON.1 (K), Reset.1; also elsewhere on the board
unnamed 35: ON.2 (A); also elsewhere on the board

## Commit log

2025-11-30 Upload ESP32 project files
2025-11-30 drag and drop
    uploading the images
2026-03-10 Added KiCad projects (Arduino Nano, ESP32, Motor speed controller)
2026-03-10 Added new PCB projects
